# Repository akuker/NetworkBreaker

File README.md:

# NetworkBreaker
Simple USB device for physically breaking/switching Ethernet signals programatically

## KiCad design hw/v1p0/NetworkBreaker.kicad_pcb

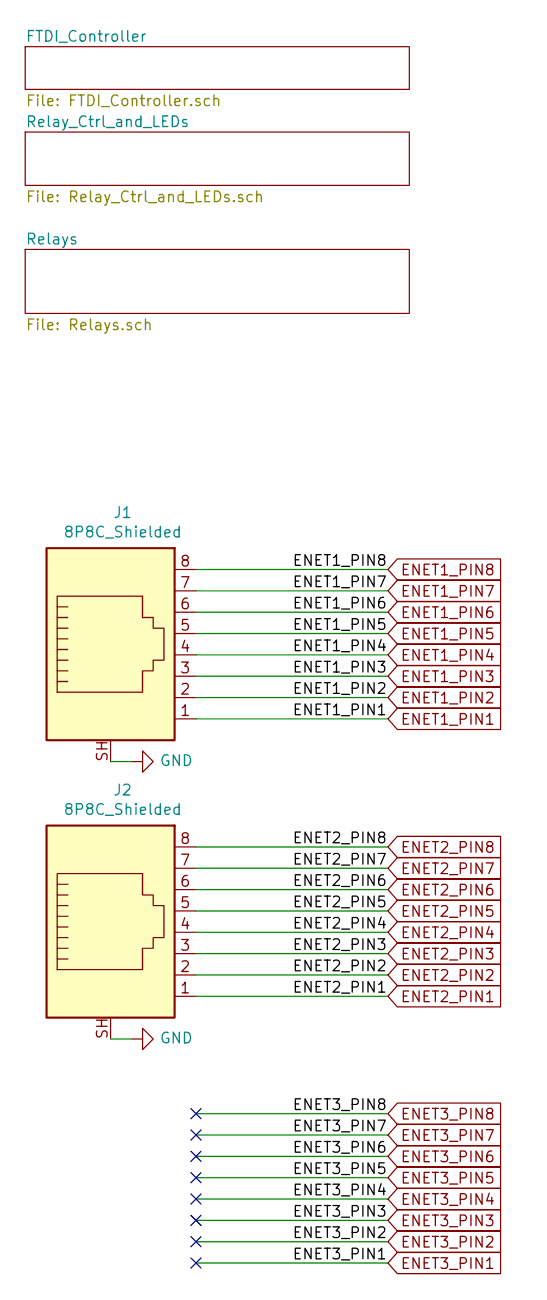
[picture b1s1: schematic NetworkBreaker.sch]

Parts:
J1, J2: 8P8C_Shielded; RJ45_Amphenol_RJHSE5380; LCSC C86575

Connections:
ENET1_PIN1: J1.1; also elsewhere on the board
ENET1_PIN2: J1.2; also elsewhere on the board
ENET1_PIN3: J1.3; also elsewhere on the board
ENET1_PIN4: J1.4; also elsewhere on the board
ENET1_PIN5: J1.5; also elsewhere on the board
ENET1_PIN6: J1.6; also elsewhere on the board
ENET1_PIN7: J1.7; also elsewhere on the board
ENET1_PIN8: J1.8; also elsewhere on the board
ENET2_PIN1: J2.1; also elsewhere on the board
ENET2_PIN2: J2.2; also elsewhere on the board
ENET2_PIN3: J2.3; also elsewhere on the board
ENET2_PIN4: J2.4; also elsewhere on the board
ENET2_PIN5: J2.5; also elsewhere on the board
ENET2_PIN6: J2.6; also elsewhere on the board
ENET2_PIN7: J2.7; also elsewhere on the board
ENET2_PIN8: J2.8; also elsewhere on the board
GND: J1.SH, J2.SH; also elsewhere on the board

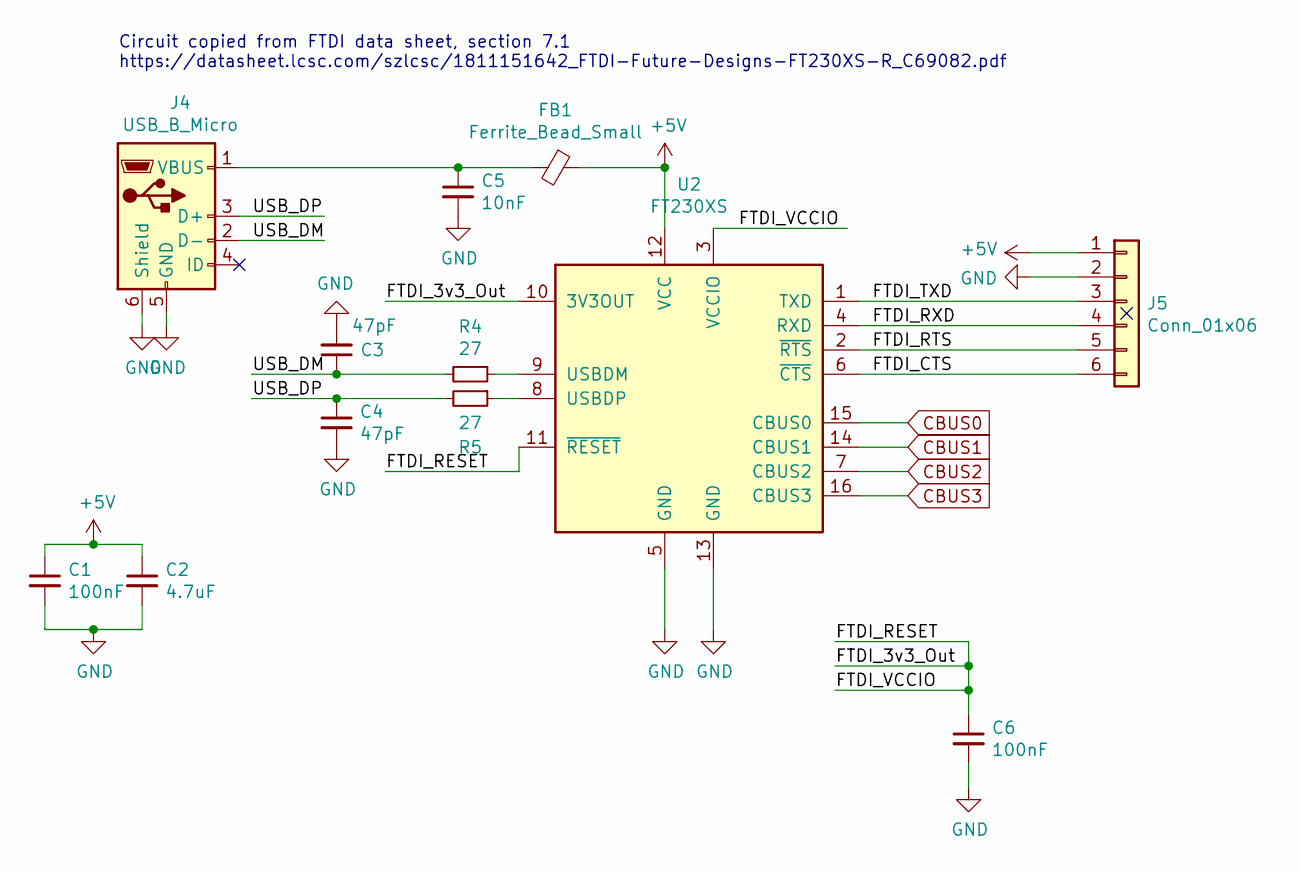
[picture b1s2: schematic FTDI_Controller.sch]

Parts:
C1, C6: 100nF; C_0805_2012Metric; LCSC C83055
C2: 4.7uF; C_1206_3216Metric; LCSC C123664
C3, C4: 47pF; C_0805_2012Metric; LCSC C123648
C5: 10nF; C_0805_2012Metric; LCSC C83058
FB1: Ferrite_Bead_Small; R_0805_2012Metric_Pad1.15x1.40mm_HandSolder; LCSC C74487
J4: USB_B_Micro; USB_Micro-B_Wuerth_629105150521; LCSC C319170
J5: Conn_01x06; PinHeader_2x03_P1.00mm_Vertical_SMD
R4, R5: 27; R_0805_2012Metric; LCSC C413252
U2: FT230XS; SSOP-16_3.9x4.9mm_P0.635mm; LCSC C69082

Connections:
+5V: C1.1, C2.1, FB1.1, J5.1, U2.12 (VCC); also elsewhere on the board
/FTDI_Controller/FTDI_3v3_Out: C6.1, U2.3 (VCCIO), U2.10 (3V3OUT), U2.11 (~RESET)
/FTDI_Controller/FTDI_CTS: J5.6, U2.6 (~CTS)
/FTDI_Controller/FTDI_RTS: J5.5, U2.2 (~RTS)
/FTDI_Controller/FTDI_RXD: J5.4, U2.4 (RXD)
/FTDI_Controller/FTDI_TXD: J5.3, U2.1 (TXD)
/FTDI_Controller/USB_DM: C3.1, J4.2 (D-), R4.2
/FTDI_Controller/USB_DP: C4.1, J4.3 (D+), R5.2
CBUS0: U2.15 (CBUS0); also elsewhere on the board
CBUS1: U2.14 (CBUS1); also elsewhere on the board
CBUS2: U2.7 (CBUS2); also elsewhere on the board
CBUS3: U2.16 (CBUS3); also elsewhere on the board
GND: C1.2, C2.2, C3.2, C4.2, C5.2, C6.2, J4.5 (GND), J4.6 (Shield), J5.2, U2.5 (GND), U2.13 (GND); also elsewhere on the board
unnamed: C5.1, FB1.2, J4.1 (VBUS)
unnamed: R4.1, U2.9 (USBDM)
unnamed: R5.1, U2.8 (USBDP)

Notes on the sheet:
Circuit copied from FTDI data sheet, section 7.1 https://datasheet.lcsc.com/szlcsc/1811151642_FTDI-Future-Designs-FT230XS-R_C69082.pdf

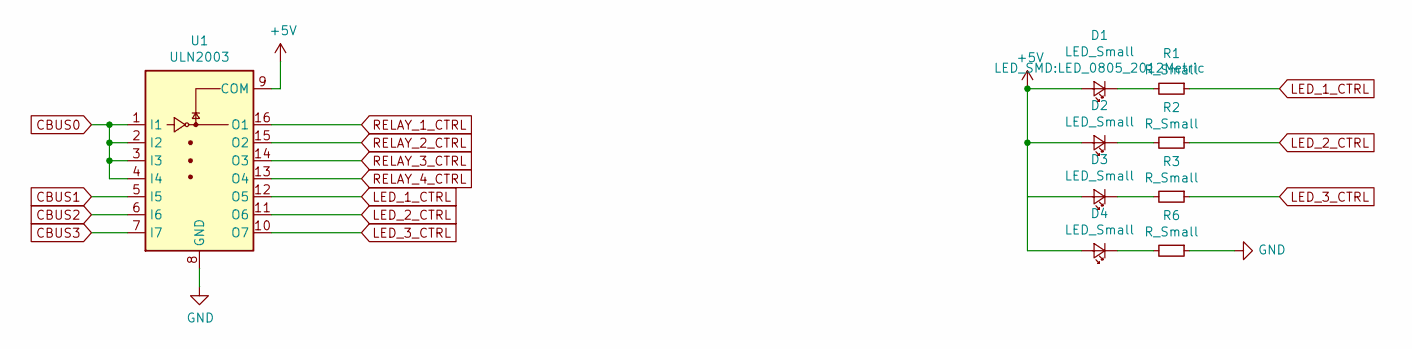
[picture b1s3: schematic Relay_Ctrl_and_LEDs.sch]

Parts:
D1, D2, D3, D4: LED_Small; LED_0805_2012Metric
R1, R2, R3, R6: R_Small; R_0805_2012Metric
U1: ULN2003; TSSOP-16_4.4x5mm_P0.65mm; LCSC C72751

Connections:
+5V: D1.2 (A), D2.2 (A), D3.2 (A), D4.2 (A), U1.9 (COM); also elsewhere on the board
CBUS0: U1.1 (I1), U1.2 (I2), U1.3 (I3), U1.4 (I4); also elsewhere on the board
CBUS1: U1.5 (I5); also elsewhere on the board
CBUS2: U1.6 (I6); also elsewhere on the board
CBUS3: U1.7 (I7); also elsewhere on the board
GND: R6.1, U1.8 (GND); also elsewhere on the board
LED_1_CTRL: R1.1, U1.12 (O5)
LED_2_CTRL: R2.1, U1.11 (O6)
LED_3_CTRL: R3.1, U1.10 (O7)
unnamed: D1.1 (K), R1.2
unnamed: D2.1 (K), R2.2
unnamed: D3.1 (K), R3.2
unnamed: D4.1 (K), R6.2
RELAY_1_CTRL: U1.16 (O1); also elsewhere on the board
RELAY_2_CTRL: U1.15 (O2); also elsewhere on the board
RELAY_3_CTRL: U1.14 (O3); also elsewhere on the board
RELAY_4_CTRL: U1.13 (O4); also elsewhere on the board

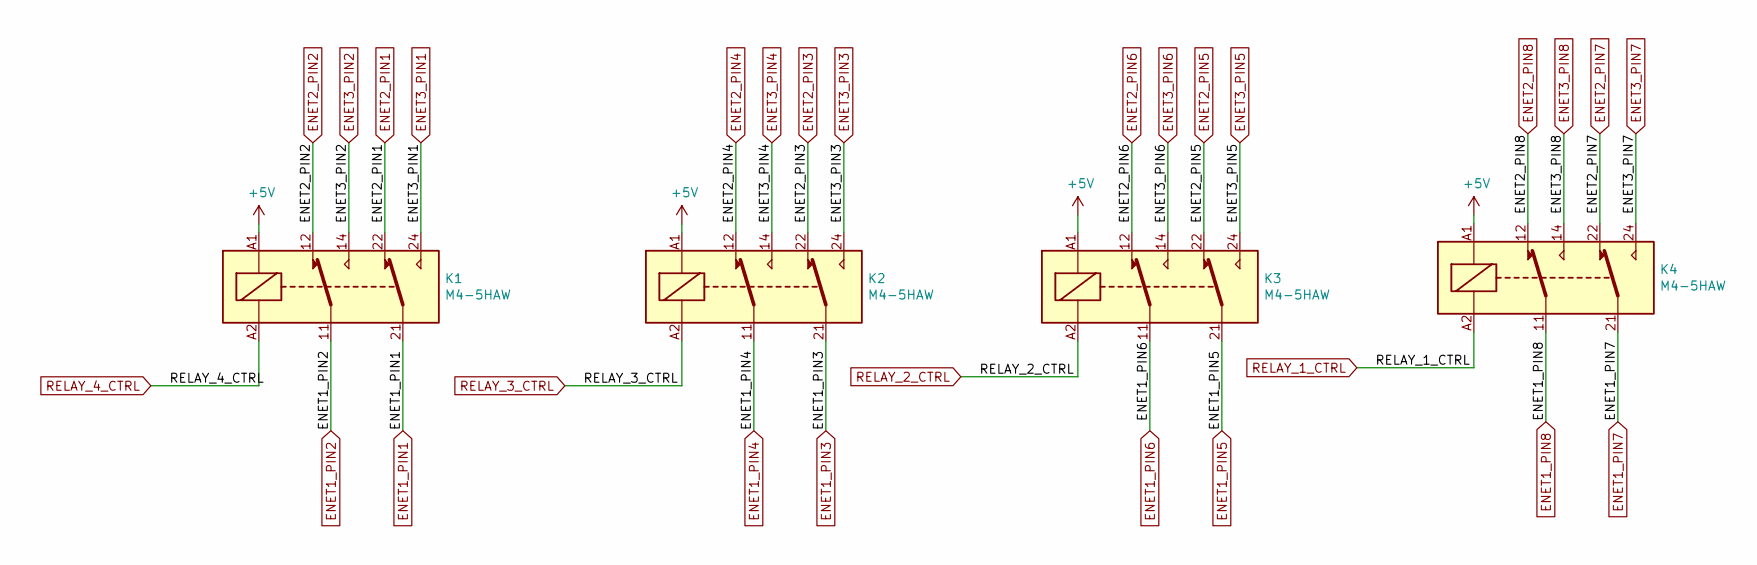
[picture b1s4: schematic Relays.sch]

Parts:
K1, K2, K3, K4: M4-5HAW; Relay_DPDT_Finder_30.22; LCSC C165868

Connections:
+5V: K1.A1, K2.A1, K3.A1, K4.A1; also elsewhere on the board
ENET1_PIN1: K1.21; also elsewhere on the board
ENET1_PIN2: K1.11; also elsewhere on the board
ENET1_PIN3: K2.21; also elsewhere on the board
ENET1_PIN4: K2.11; also elsewhere on the board
ENET1_PIN5: K3.21; also elsewhere on the board
ENET1_PIN6: K3.11; also elsewhere on the board
ENET1_PIN7: K4.21; also elsewhere on the board
ENET1_PIN8: K4.11; also elsewhere on the board
ENET2_PIN1: K1.22; also elsewhere on the board
ENET2_PIN2: K1.12; also elsewhere on the board
ENET2_PIN3: K2.22; also elsewhere on the board
ENET2_PIN4: K2.12; also elsewhere on the board
ENET2_PIN5: K3.22; also elsewhere on the board
ENET2_PIN6: K3.12; also elsewhere on the board
ENET2_PIN7: K4.22; also elsewhere on the board
ENET2_PIN8: K4.12; also elsewhere on the board
ENET3_PIN1: K1.24
ENET3_PIN2: K1.14
ENET3_PIN3: K2.24
ENET3_PIN4: K2.14
ENET3_PIN5: K3.24
ENET3_PIN6: K3.14
ENET3_PIN7: K4.24
ENET3_PIN8: K4.14
RELAY_1_CTRL: K4.A2; also elsewhere on the board
RELAY_2_CTRL: K3.A2; also elsewhere on the board
RELAY_3_CTRL: K2.A2; also elsewhere on the board
RELAY_4_CTRL: K1.A2; also elsewhere on the board

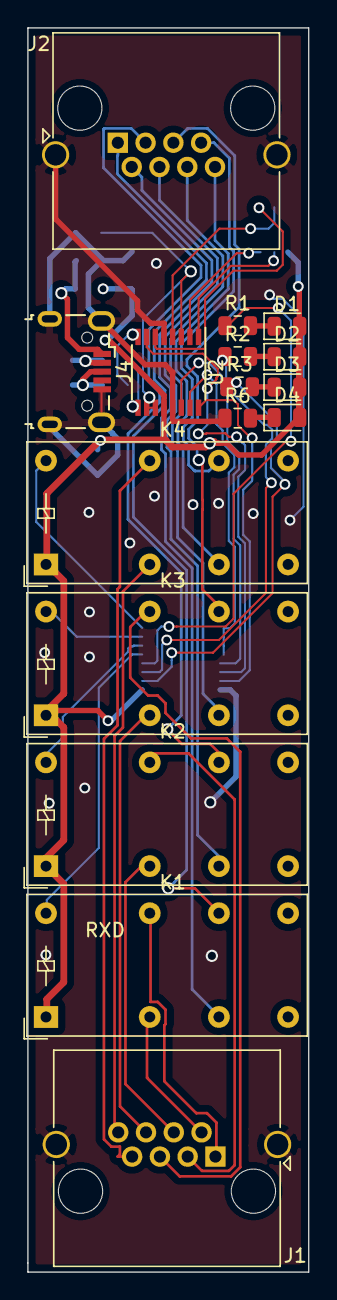
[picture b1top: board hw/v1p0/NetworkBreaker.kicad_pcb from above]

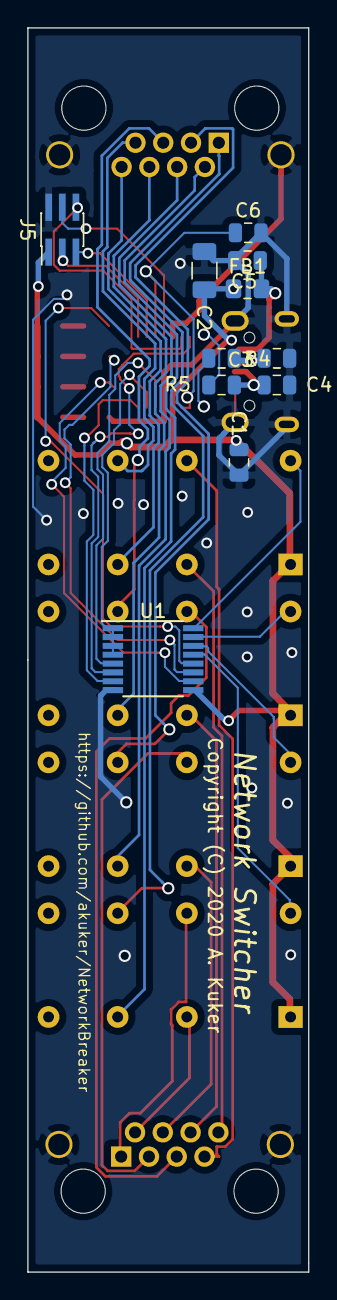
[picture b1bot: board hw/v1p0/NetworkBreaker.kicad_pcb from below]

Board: 2 copper layers, 20.6 x 91.4 mm, 27 parts (11 on the bottom side), 43 nets.

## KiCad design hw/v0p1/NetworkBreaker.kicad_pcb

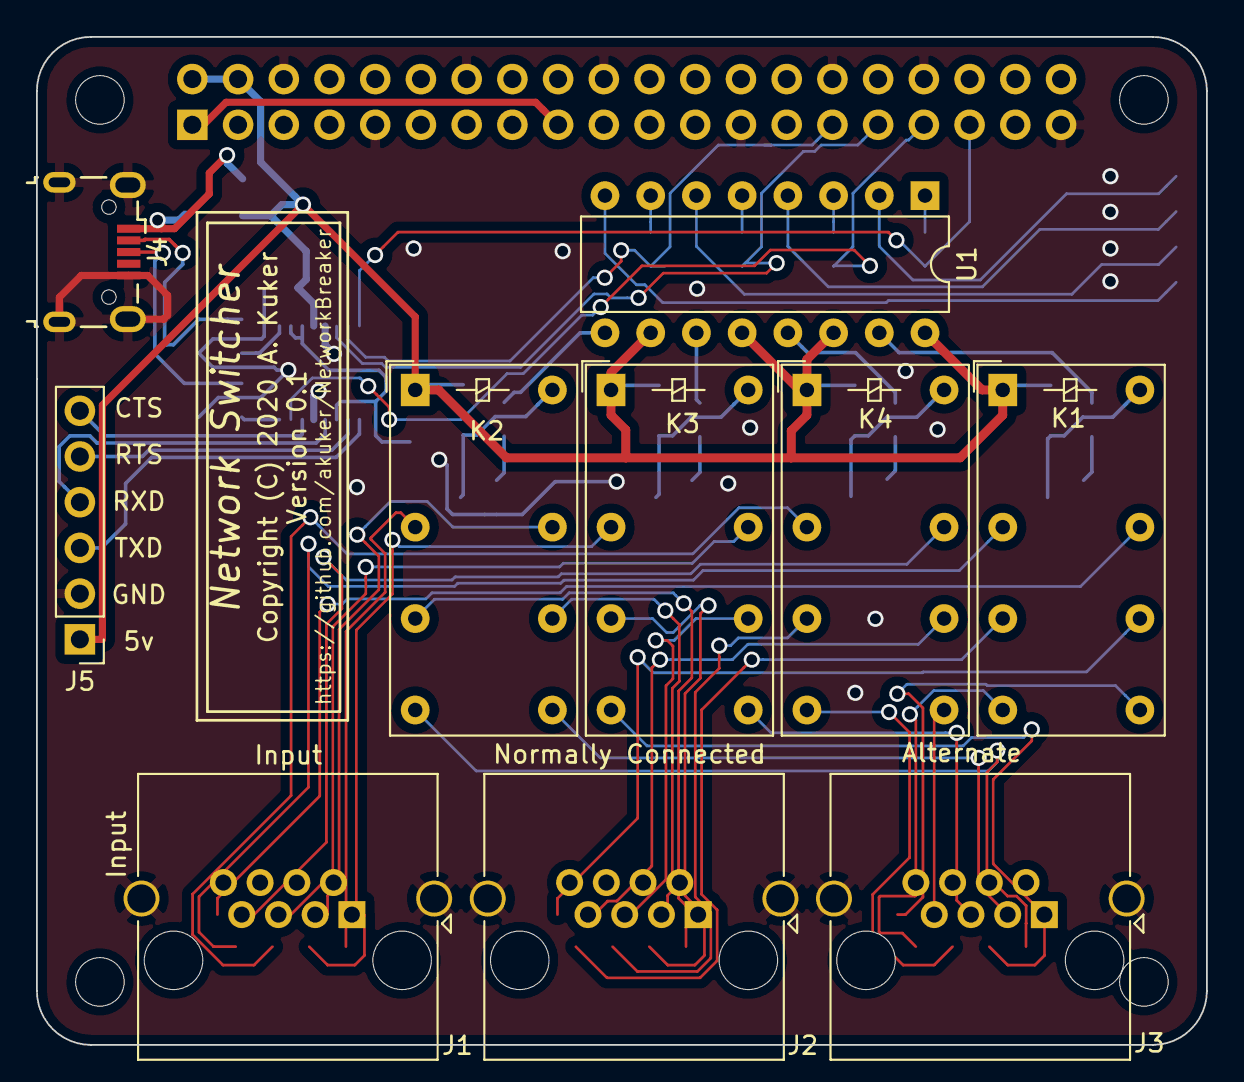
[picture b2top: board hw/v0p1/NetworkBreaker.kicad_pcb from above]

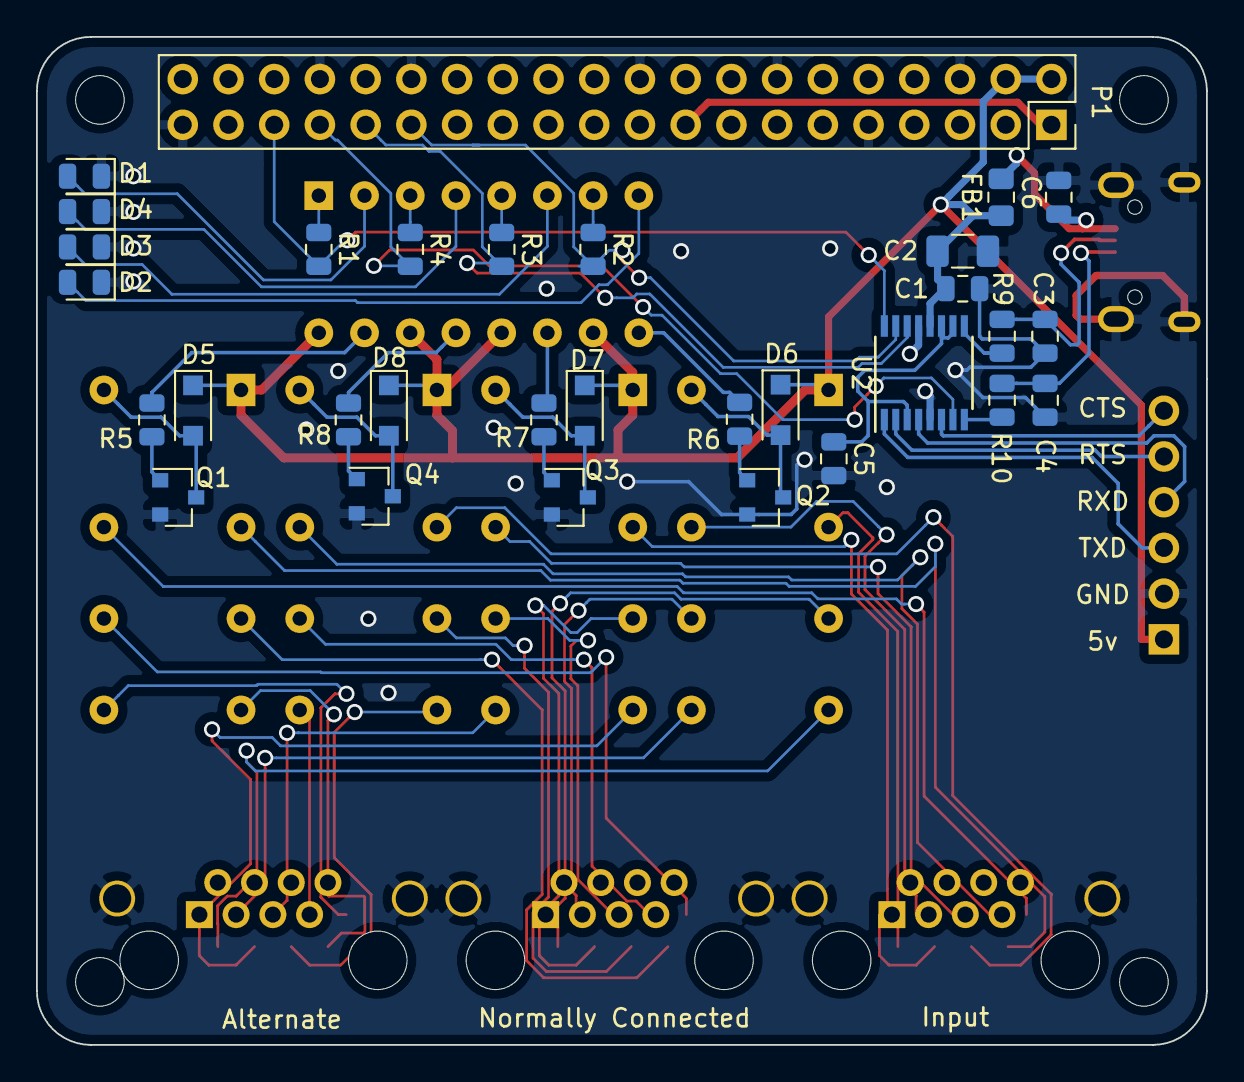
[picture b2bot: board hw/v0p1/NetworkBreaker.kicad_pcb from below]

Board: 2 copper layers, 65.0 x 56.0 mm, 45 parts (31 on the bottom side), 61 nets.

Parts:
C1, C5: 100nF; C_0805_2012Metric
C2: 4.7uF; C_1206_3216Metric
C3, C4: 47pF; C_0805_2012Metric
C6: 10nF; C_0805_2012Metric
D1, D2, D3, D4: Green; LED_0805_2012Metric
D5, D6, D7, D8: D_Small; D_SOD-123F
FB1: Ferrite_Bead_Small; R_0805_2012Metric_Pad1.15x1.40mm_HandSolder
J1, J2, J3: 8P8C_Shielded; RJ45_Amphenol_RJHSE5380
J4: USB_B_Micro; USB_Micro-B_Wuerth_629105150521
J5: Conn_01x06; PinHeader_1x06_P2.54mm_Vertical
K1, K2, K3, K4: M4-5HAW; Relay_DPDT_Finder_30.22
MK1, MK2, MK3, MK4: M2.5; MountingHole_2.7mm_M2.5
P1: Conn_02x20_Odd_Even; PinSocket_2x20_P2.54mm_Vertical
Q1, Q2, Q3, Q4: 2N3904; SOT-23
R1, R2, R3, R4: 220; R_0805_2012Metric
R5, R6, R7, R8: 10k; R_0805_2012Metric
R9, R10: 27; R_0805_2012Metric
U1: TLP627-4; DIP-16_W7.62mm
U2: FT230XS; SSOP-16_3.9x4.9mm_P0.635mm

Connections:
+3V3: P1.1, P1.17
+5V: C1.1, C2.1, D5.1, D6.1, D7.1, D8.1, FB1.1, J5.1, K1.A1, K2.A1, K3.A1, K4.A1, P1.2, P1.4, U1.10, U1.12, U1.14, U1.16, U2.12
/ENET1_PIN1: J1.1, K1.21
/ENET1_PIN2: J1.2, K1.11
/ENET1_PIN3: J1.3, K4.21
/ENET1_PIN4: J1.4, K4.11
/ENET1_PIN5: J1.5, K3.21
/ENET1_PIN6: J1.6, K3.11
/ENET1_PIN7: J1.7, K2.21
/ENET1_PIN8: J1.8, K2.11
/ENET2_PIN1: J2.1, K1.22
/ENET2_PIN2: J2.2, K1.12
/ENET2_PIN3: J2.3, K4.22
/ENET2_PIN4: J2.4, K4.12
/ENET2_PIN5: J2.5, K3.22
/ENET2_PIN6: J2.6, K3.12
/ENET2_PIN7: J2.7, K2.22
/ENET2_PIN8: J2.8, K2.12
/ENET3_PIN1: J3.1, K1.24
/ENET3_PIN2: J3.2, K1.14
/ENET3_PIN3: J3.3, K4.24
/ENET3_PIN4: J3.4, K4.14
/ENET3_PIN5: J3.5, K3.24
/ENET3_PIN6: J3.6, K3.14
/ENET3_PIN7: J3.7, K2.24
/ENET3_PIN8: J3.8, K2.14
/FTDI_Controller/FTDI_3v3_Out: C5.1, U2.3, U2.10, U2.11
/FTDI_Controller/FTDI_CTS: J5.6, U2.6
/FTDI_Controller/FTDI_RTS: J5.5, U2.2
/FTDI_Controller/FTDI_RXD: J5.4, U2.4
/FTDI_Controller/FTDI_TXD: J5.3, U2.1
/FTDI_Controller/USB_DM: C3.1, J4.2, R9.2
/FTDI_Controller/USB_DP: C4.1, J4.3, R10.2
GND: C1.2, C2.2, C3.2, C4.2, C5.2, C6.2, D1.1, D2.1, D3.1, D4.1, J1.SH, J2.SH, J3.SH, J4.5, J4.6, J5.2, P1.6, P1.9, P1.14, P1.20, P1.25, P1.30, P1.34, P1.39, Q1.2, Q2.2, Q3.2, Q4.2, U2.5, U2.13
GPIO5: P1.29, R2.2, U2.15
GPIO6: P1.31, R3.2, U2.14
GPIO13: P1.33, R4.2, U2.7
GPIO19: P1.35, R1.2, U2.16
unnamed: C6.1, FB1.2, J4.1
unnamed: D1.2, U1.2
unnamed: D2.2, U1.8
unnamed: D3.2, U1.6
unnamed: D4.2, U1.4
unnamed: D5.2, K1.A2, Q1.3
unnamed: D6.2, K2.A2, Q2.3
unnamed: D7.2, K3.A2, Q3.3
unnamed: D8.2, K4.A2, Q4.3
unnamed: Q1.1, R5.1
unnamed: Q2.1, R6.1
unnamed: Q3.1, R7.1
unnamed: Q4.1, R8.1
unnamed: R1.1, U1.1
unnamed: R2.1, U1.7
unnamed: R3.1, U1.5
unnamed: R4.1, U1.3
unnamed: R5.2, U1.15
unnamed: R6.2, U1.9
unnamed: R7.2, U1.11
unnamed: R8.2, U1.13
unnamed: R9.1, U2.9
unnamed: R10.1, U2.8

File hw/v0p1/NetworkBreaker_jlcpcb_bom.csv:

Comment,Designator,Footprint,LCSC
"100nF","C1,C5","Capacitor_SMD:C_0805_2012Metric","C83055"
"4.7uF","C2","Capacitor_SMD:C_1206_3216Metric","C123664"
"47pF","C3,C4","Capacitor_SMD:C_0805_2012Metric","C123648"
"10nF","C6","Capacitor_SMD:C_0805_2012Metric","C83058"
"Green","D1,D2,D3,D4","LED_SMD:LED_0805_2012Metric"," C125090"
"D_Small","D5,D6,D7,D8","Diode_SMD:D_SOD-123F","C108803"
"Ferrite_Bead_Small","FB1","Resistor_SMD:R_0805_2012Metric_Pad1.15x1.40mm_HandSolder","C74487"
"8P8C_Shielded","J1,J2,J3","Connector_RJ:RJ45_Amphenol_RJHSE5380","C86575"
"USB_B_Micro","J4","Connector_USB:USB_Micro-B_Wuerth_629105150521","C319170"
"Conn_01x06","J5","Connector_PinHeader_2.54mm:PinHeader_1x06_P2.54mm_Vertical",""
"M4-5HAW","K1,K2,K3,K4","Relay_THT:Relay_DPDT_Finder_30.22","C165868"
"M2.5","MK1,MK2,MK3,MK4","MountingHole:MountingHole_2.7mm_M2.5",""
"Conn_02x20_Odd_Even","P1","Connector_PinSocket_2.54mm:PinSocket_2x20_P2.54mm_Vertical","C50982"
"2N3904","Q1,Q2,Q3,Q4","Package_TO_SOT_SMD:SOT-23","C18536"
"220","R1,R2,R3,R4","Resistor_SMD:R_0805_2012Metric","C413172"
"10k","R5,R6,R7,R8","Resistor_SMD:R_0805_2012Metric","C180849"
"27","R9,R10","Resistor_SMD:R_0805_2012Metric","C413252"
"TLP627-4","U1","Package_DIP:DIP-16_W7.62mm","C89243"
"FT230XS","U2","Package_SO:SSOP-16_3.9x4.9mm_P0.635mm","C69082"

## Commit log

2020-08-22 First version of network breaker
2020-08-22 Updated BOM
2020-08-23 Updated part LCSC part numbers
2020-09-07 Initial round of corrections from v0.1
2020-09-12 Version 1.0 of breaker only

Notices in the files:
hw/v0p1/NetworkBreaker.kicad_pcb:
Copyright (C) 2020 A. Kuker
